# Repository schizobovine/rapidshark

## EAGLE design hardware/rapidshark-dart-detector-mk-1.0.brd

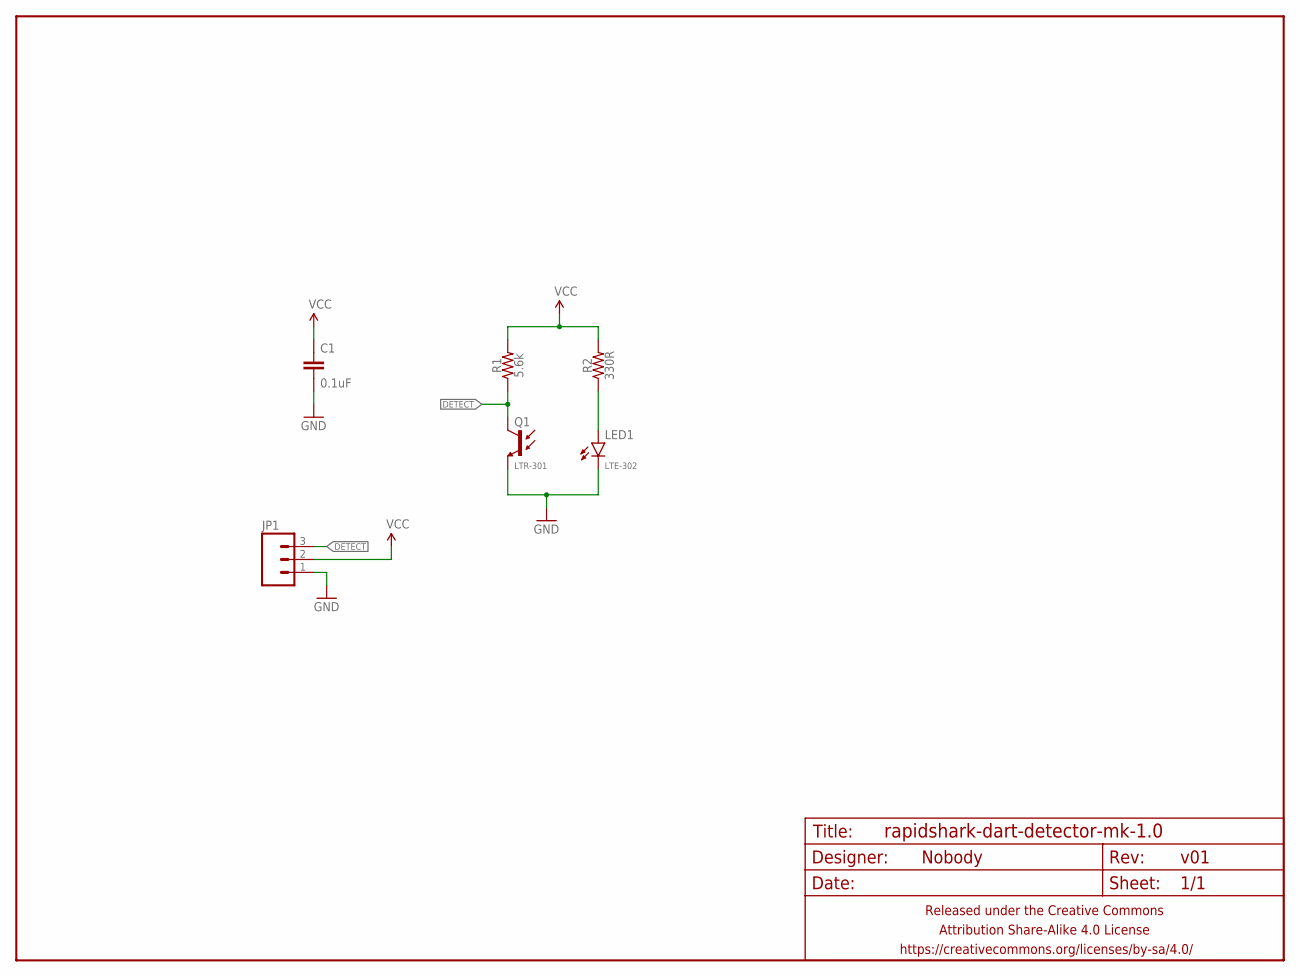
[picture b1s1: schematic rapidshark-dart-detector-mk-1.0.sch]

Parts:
C1: 0.1uF; C0805
FRAME1: FRAME-LETTERNO_PACKAGE; DUMMY
JP1: M03JST-PTH; JST-3-PH-RA-PTH
LED1: LTE-302; LED-2.54MM
Q1: LTR-301; LED-2.54MM
R1: 5.6k; R0805
R2: 330R; R0805

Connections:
DETECT: JP1.3, Q1.A (C), R1.1
GND: C1.2, JP1.1, LED1.K (C), Q1.K (E)
unnamed: LED1.A, R2.1
VCC: C1.1, JP1.2, R1.2, R2.2

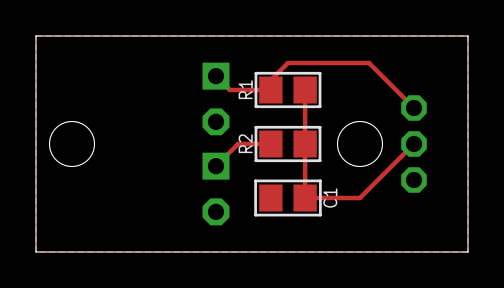
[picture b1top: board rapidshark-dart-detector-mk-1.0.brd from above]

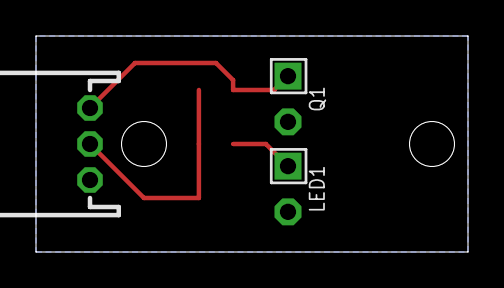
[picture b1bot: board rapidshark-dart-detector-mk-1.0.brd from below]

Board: 2 copper layers, 24.0 x 12.0 mm, 7 parts (3 on the bottom side), 4 nets.

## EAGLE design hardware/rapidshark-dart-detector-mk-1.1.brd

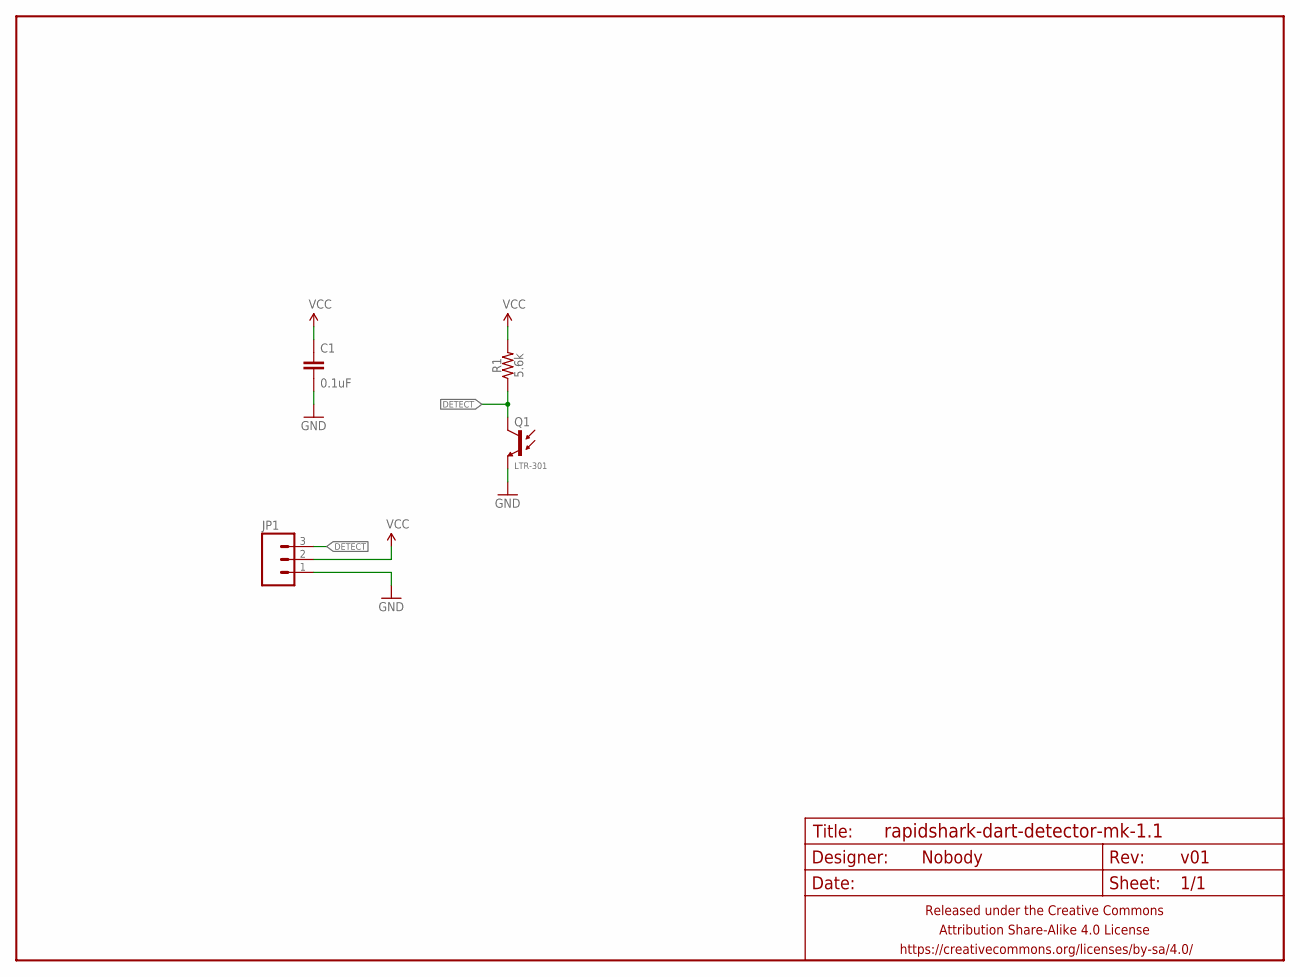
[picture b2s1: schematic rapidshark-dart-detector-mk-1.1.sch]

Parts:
C1: 0.1uF; C025-024X044
FRAME1: FRAME-LETTERNO_PACKAGE; DUMMY
JP1: M03JST-PTH; JST-3-PH-RA-PTH
Q1: LTR-301; LED-2.54MM-SIDE
R1: 5.6k; RESISTOR-AXIAL-PTH-6.35MM

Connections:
DETECT: JP1.3, Q1.A (C), R1.P$1 (1)
GND: C1.2, JP1.1, Q1.K (E)
VCC: C1.1, JP1.2, R1.P$2 (2)

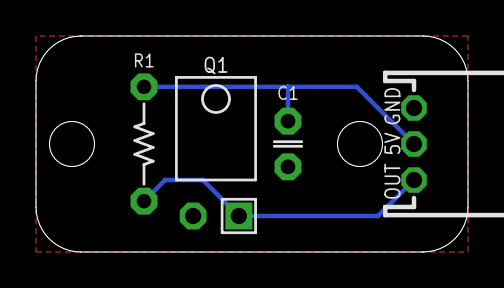
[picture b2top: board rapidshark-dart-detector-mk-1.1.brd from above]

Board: 2 copper layers, 24.0 x 12.0 mm, 5 parts (1 on the bottom side), 3 nets.

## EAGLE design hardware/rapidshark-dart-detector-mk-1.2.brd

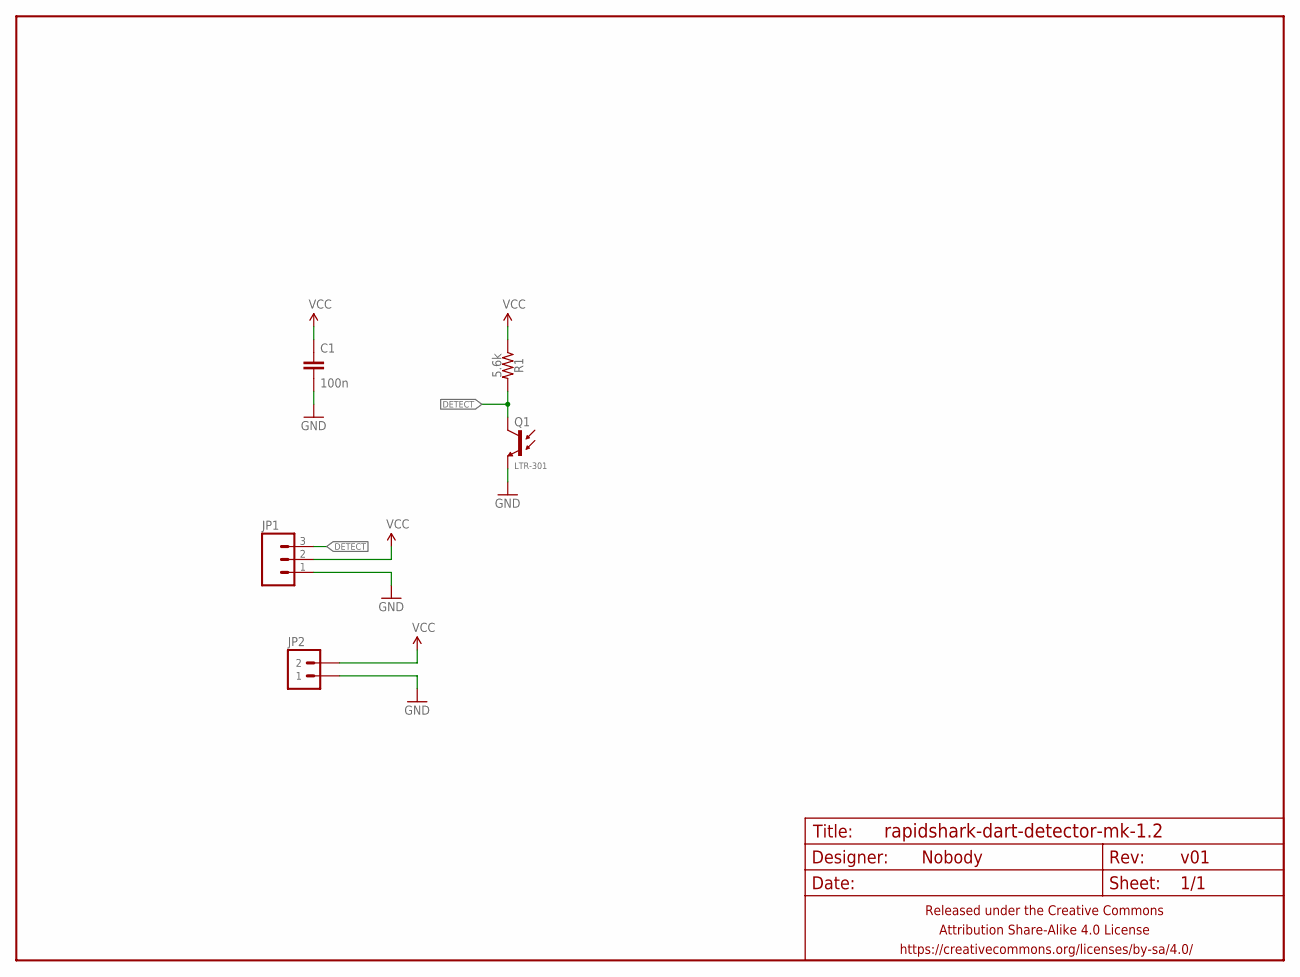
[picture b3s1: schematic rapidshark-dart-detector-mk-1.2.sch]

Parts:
C1: 100n; C025-024X044
FRAME1: FRAME-LETTERNO_PACKAGE; DUMMY
JP1: M03JST-PTH; JST-3-PH-RA-PTH
JP2: M02JST-PTH-RA-R+; JST-2-PH-RA-PTH-R+
Q1: LTR-301; LED-2.54MM-SIDE
R1: 5.6k; RESISTOR-AXIAL-PTH-5.08MM

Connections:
DETECT: JP1.3, Q1.A (C), R1.P$2 (2)
GND: C1.2, JP1.1, JP2.1, Q1.K (E)
VCC: C1.1, JP1.2, JP2.2, R1.P$1 (1)

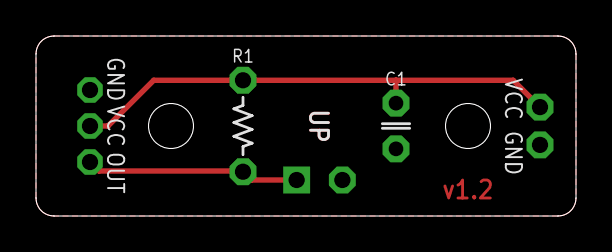
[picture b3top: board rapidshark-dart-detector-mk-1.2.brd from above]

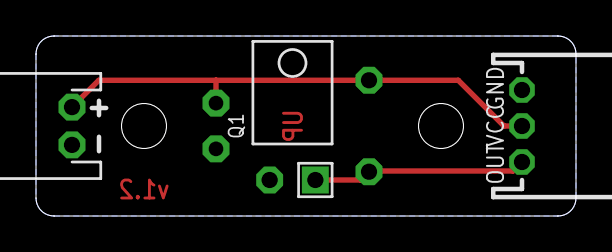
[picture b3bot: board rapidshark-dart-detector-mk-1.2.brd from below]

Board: 2 copper layers, 30.0 x 10.0 mm, 6 parts (3 on the bottom side), 3 nets.

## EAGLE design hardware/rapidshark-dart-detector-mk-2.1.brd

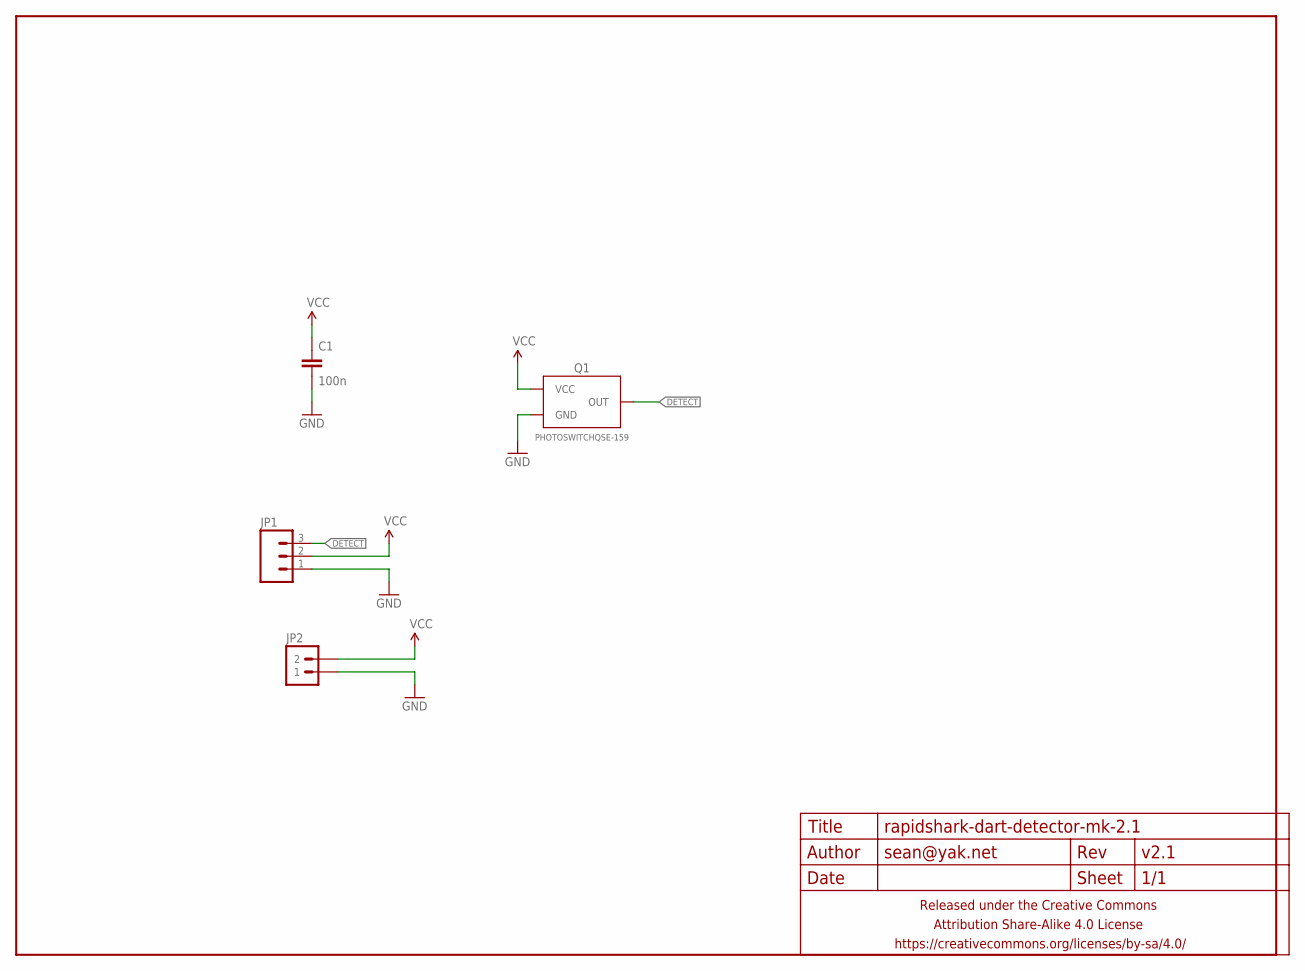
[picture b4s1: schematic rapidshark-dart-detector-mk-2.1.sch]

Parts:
C1: 100n; C025-024X044
FRAME1: FRAME-LETTERNO_PACKAGE; DUMMY
JP1: M03JST-PTH; JST-3-PH-RA-PTH
JP2: M02JST-PTH-RA-R+; JST-2-PH-RA-PTH-R+
Q1: PHOTOSWITCHQSE-159; QSE-159

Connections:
DETECT: JP1.3, Q1.2 (OUT)
GND: C1.2, JP1.1, JP2.1, Q1.1 (GND)
VCC: C1.1, JP1.2, JP2.2, Q1.3 (VCC)

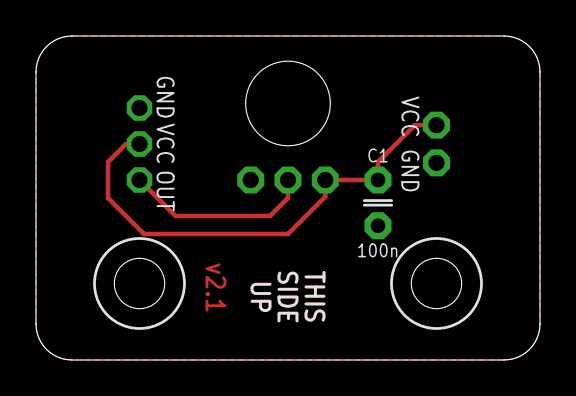
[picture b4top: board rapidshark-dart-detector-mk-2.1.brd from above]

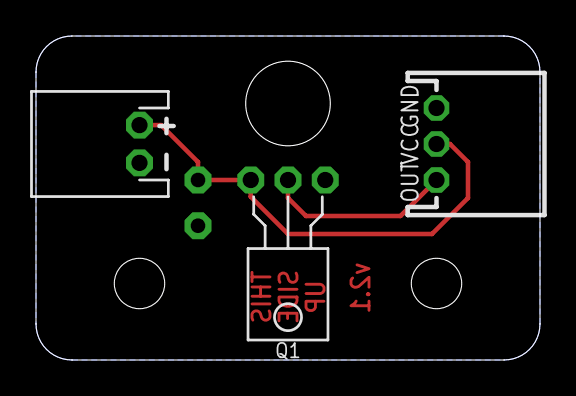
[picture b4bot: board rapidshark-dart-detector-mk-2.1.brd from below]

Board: 2 copper layers, 28.0 x 18.0 mm, 5 parts (3 on the bottom side), 3 nets.

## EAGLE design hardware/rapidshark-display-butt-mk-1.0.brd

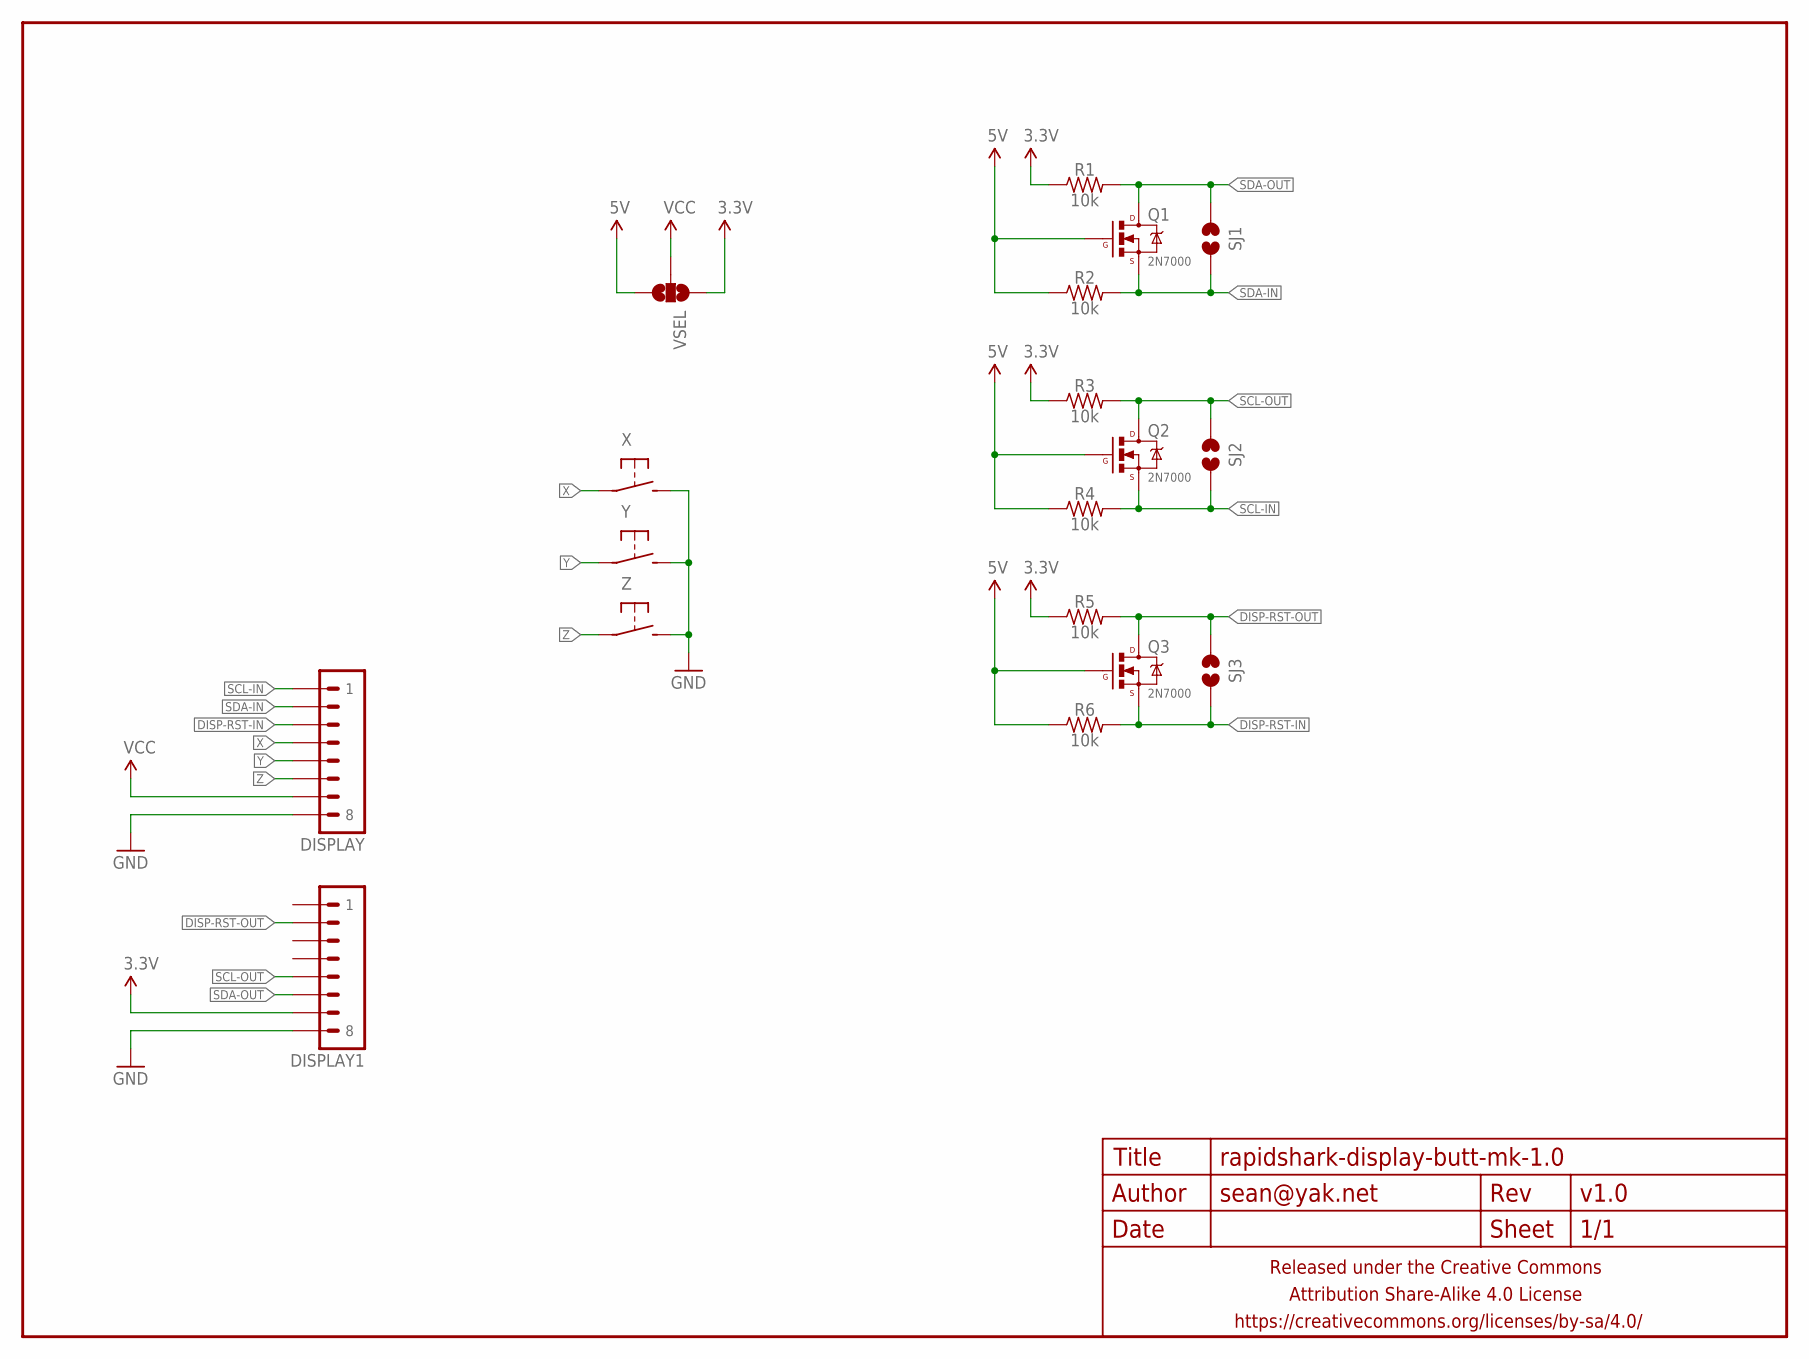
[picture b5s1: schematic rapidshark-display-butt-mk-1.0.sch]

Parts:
DISPLAY: M08JST-PH-VERT-PTH; JST-8-VERT-PTH
DISPLAY1: M081X08; 1X08
FRAME1: FRAME-LETTERNO_PACKAGE; DUMMY
Q1, Q2, Q3: 2N7000; TO-92-AMMO
R1, R2, R3, R4, R5, R6: 10k; RESISTOR-AXIAL-PTH-5.08MM
SJ1, SJ2, SJ3: JUMPER-PAD-2-NOYES_SILK; PAD-JUMPER-2-NO_YES_SILK
VSEL: JUMPER-PAD-3-NOFULL_BOX_SILK; PAD-JUMPER-3-NO_YES_SILK_FULL_BOX
X: SPST-NO-TACT6MM-PTH-SMALL-PADS; DTS-6-SMALL-PADS
Y: SPST-NO-TACT6MM-PTH-SMALL-PADS; DTS-6-SMALL-PADS
Z: SPST-NO-TACT6MM-PTH-SMALL-PADS; DTS-6-SMALL-PADS

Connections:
3.3V: DISPLAY1.7, R1.P$1 (1), R3.P$1 (1), R5.P$1 (1), VSEL.1
5V: Q1.2 (G), Q2.2 (G), Q3.2 (G), R2.P$1 (1), R4.P$1 (1), R6.P$1 (1), VSEL.3
DISP-RST-IN: DISPLAY.3, Q3.1 (S), R6.P$2 (2), SJ3.1
DISP-RST-OUT: DISPLAY1.2, Q3.3 (D), R5.P$2 (2), SJ3.2
GND: DISPLAY.8, DISPLAY1.8, X.3 (2), X.4 (2), Y.3 (2), Y.4 (2), Z.3 (2), Z.4 (2)
SCL-IN: DISPLAY.1, Q2.1 (S), R4.P$2 (2), SJ2.1
SCL-OUT: DISPLAY1.5, Q2.3 (D), R3.P$2 (2), SJ2.2
SDA-IN: DISPLAY.2, Q1.1 (S), R2.P$2 (2), SJ1.1
SDA-OUT: DISPLAY1.6, Q1.3 (D), R1.P$2 (2), SJ1.2
VCC: DISPLAY.7, VSEL.2
X: DISPLAY.4, X.1, X.2 (1)
Y: DISPLAY.5, Y.1, Y.2 (1)
Z: DISPLAY.6, Z.1, Z.2 (1)

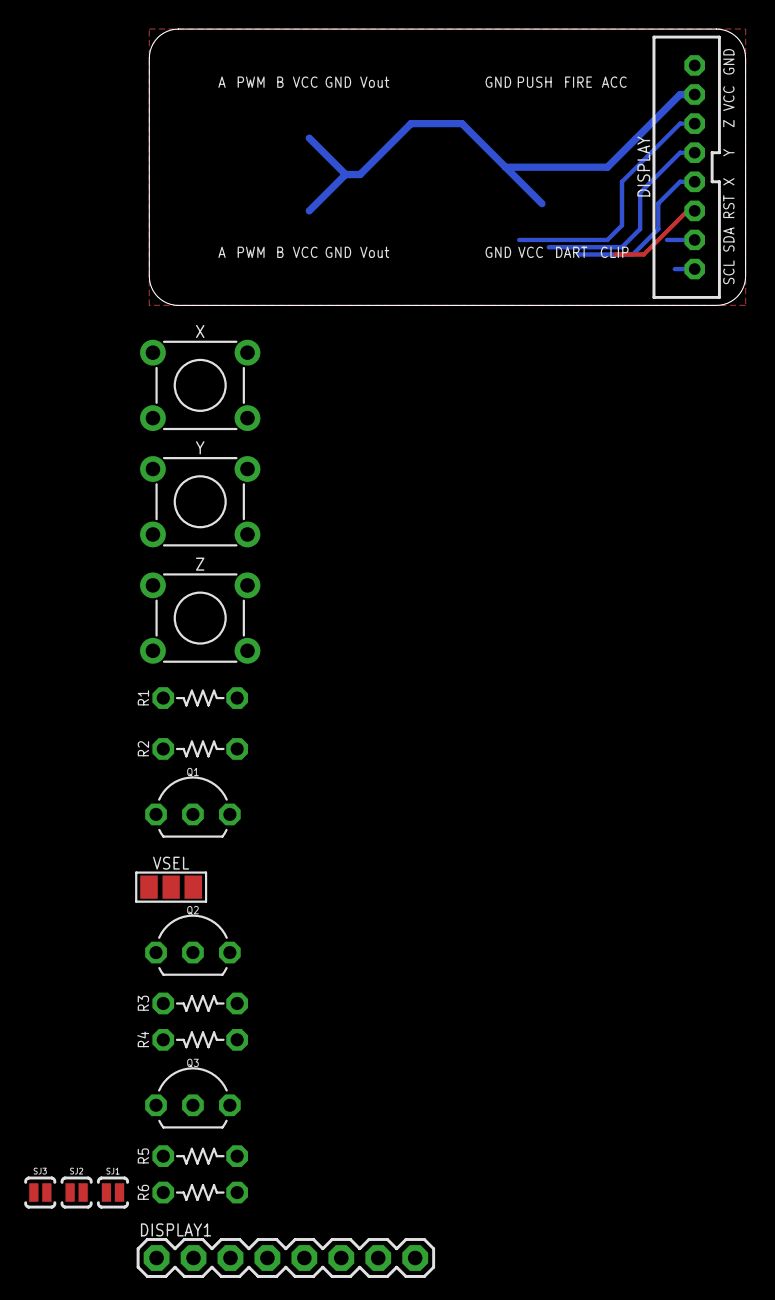
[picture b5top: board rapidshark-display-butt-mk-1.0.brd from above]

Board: 2 copper layers, 41.0 x 19.0 mm, 19 parts (1 on the bottom side), 13 nets.

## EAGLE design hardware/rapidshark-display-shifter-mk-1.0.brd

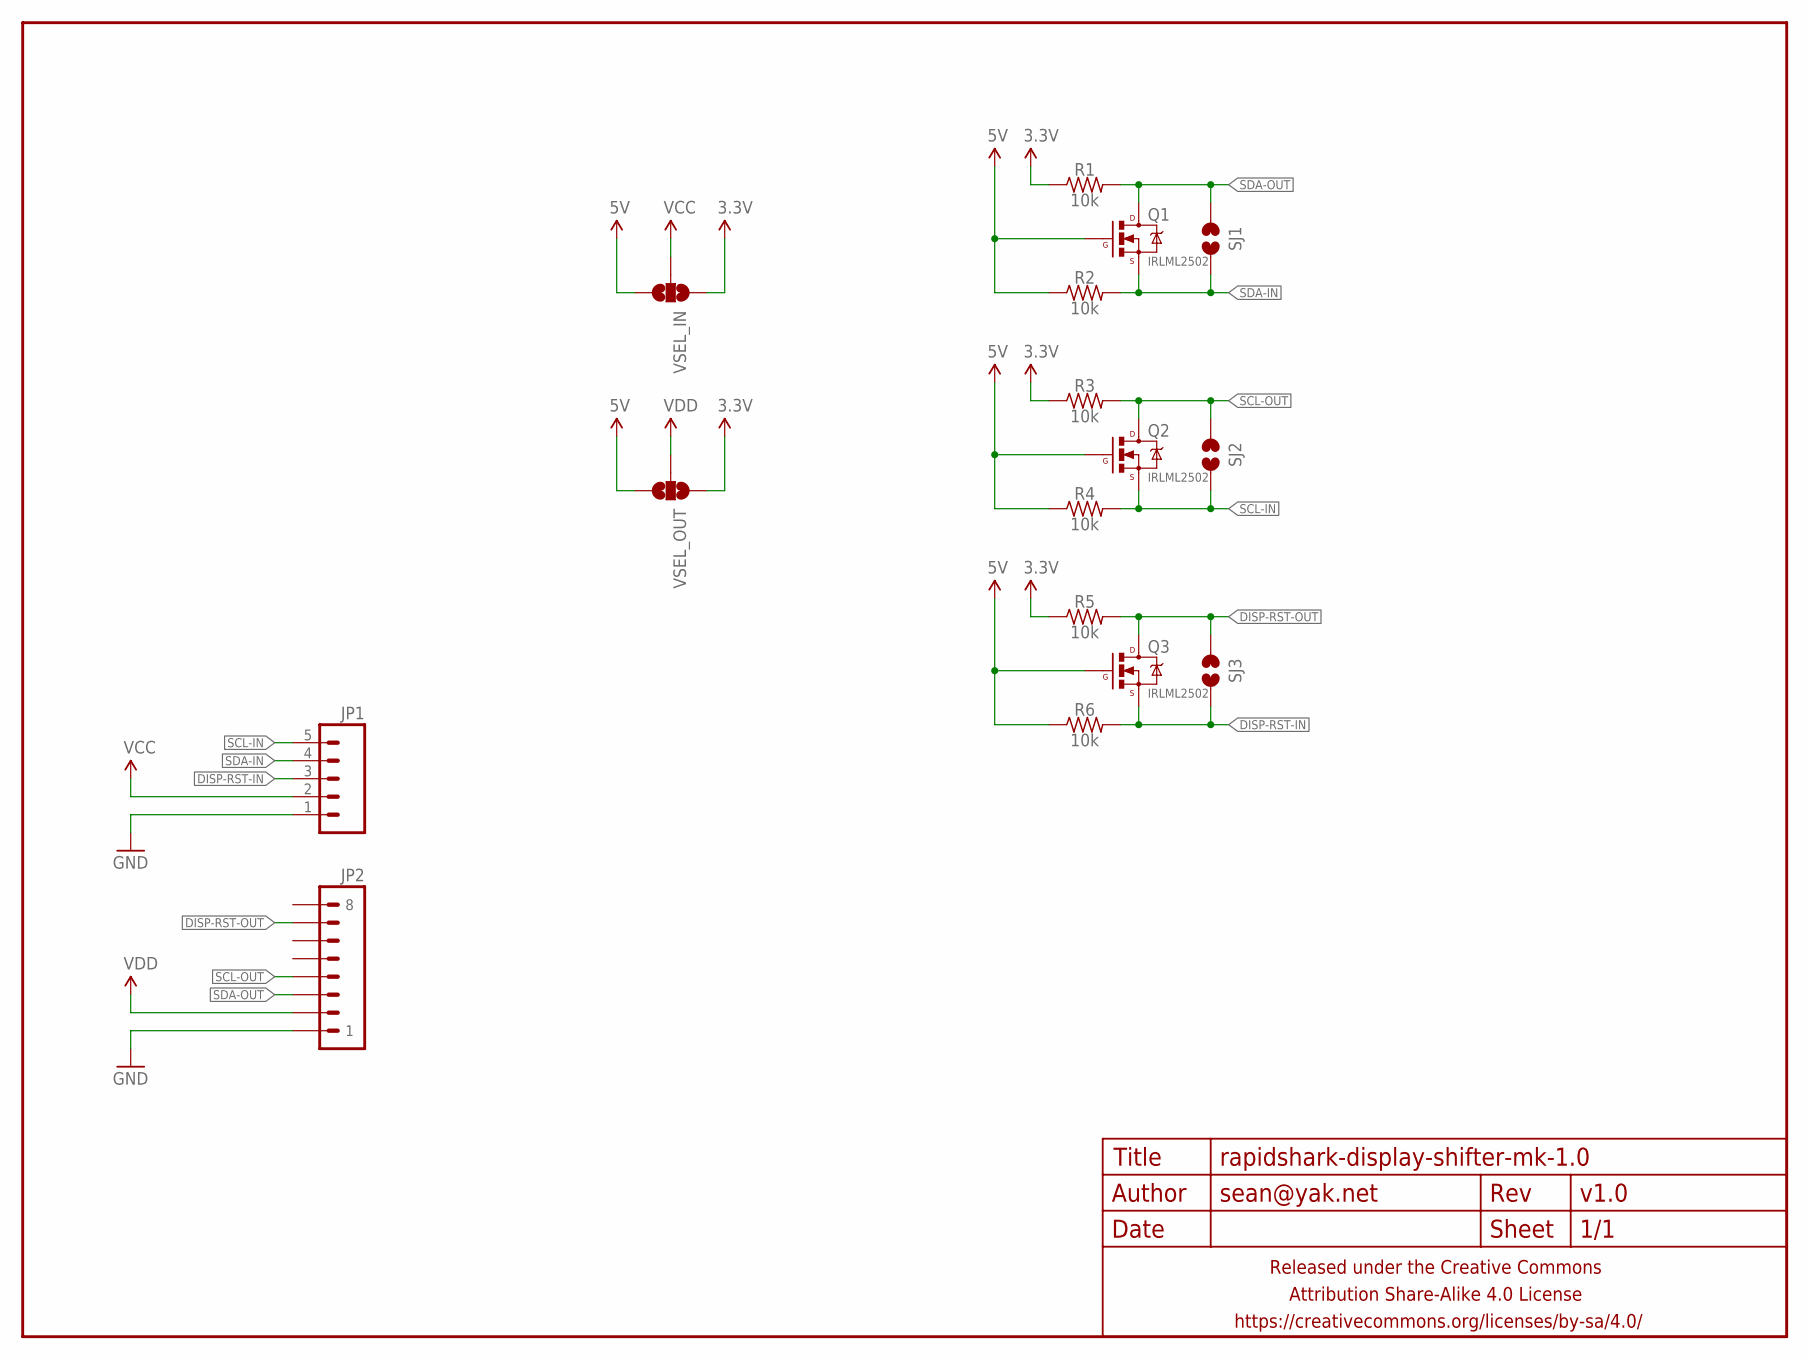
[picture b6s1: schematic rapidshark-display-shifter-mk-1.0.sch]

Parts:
FRAME1: FRAME-LETTERNO_PACKAGE; DUMMY
JP1: M05JST-PH-VERT-PTH; JST-5-PH-VERT-PTH
JP2: M081X08; 1X08
Q1, Q2, Q3: IRLML2502; SOT23
R1, R2, R3, R4, R5, R6: 10k; R0805
SJ1, SJ2, SJ3: JUMPER-PAD-2-NOYES_SILK; PAD-JUMPER-2-NO_YES_SILK
VSEL_IN: JUMPER-PAD-3-NOFULL_BOX_SILK; PAD-JUMPER-3-NO_YES_SILK_FULL_BOX
VSEL_OUT: JUMPER-PAD-3-NOFULL_BOX_SILK; PAD-JUMPER-3-NO_YES_SILK_FULL_BOX

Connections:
3.3V: R1.1, R3.1, R5.1, VSEL_IN.1, VSEL_OUT.1
5V: Q1.1 (G), Q2.1 (G), Q3.1 (G), R2.1, R4.1, R6.1, VSEL_IN.3, VSEL_OUT.3
DISP-RST-IN: JP1.3, Q3.2 (S), R6.2, SJ3.1
DISP-RST-OUT: JP2.7, Q3.3 (D), R5.2, SJ3.2
GND: JP1.1, JP2.1
SCL-IN: JP1.5, Q2.2 (S), R4.2, SJ2.1
SCL-OUT: JP2.4, Q2.3 (D), R3.2, SJ2.2
SDA-IN: JP1.4, Q1.2 (S), R2.2, SJ1.1
SDA-OUT: JP2.3, Q1.3 (D), R1.2, SJ1.2
VCC: JP1.2, VSEL_IN.2
VDD: JP2.2, VSEL_OUT.2

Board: 2 copper layers, 17 parts (1 on the bottom side), 11 nets, no tracks yet.

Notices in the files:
parts and their libraries:
A_butts: Released under the Creative Commons Attribution Share-Alike 4.0 License
A_butts: https://creativecommons.org/licenses/by-sa/4.0
A_butts: Released under the Creative Commons
